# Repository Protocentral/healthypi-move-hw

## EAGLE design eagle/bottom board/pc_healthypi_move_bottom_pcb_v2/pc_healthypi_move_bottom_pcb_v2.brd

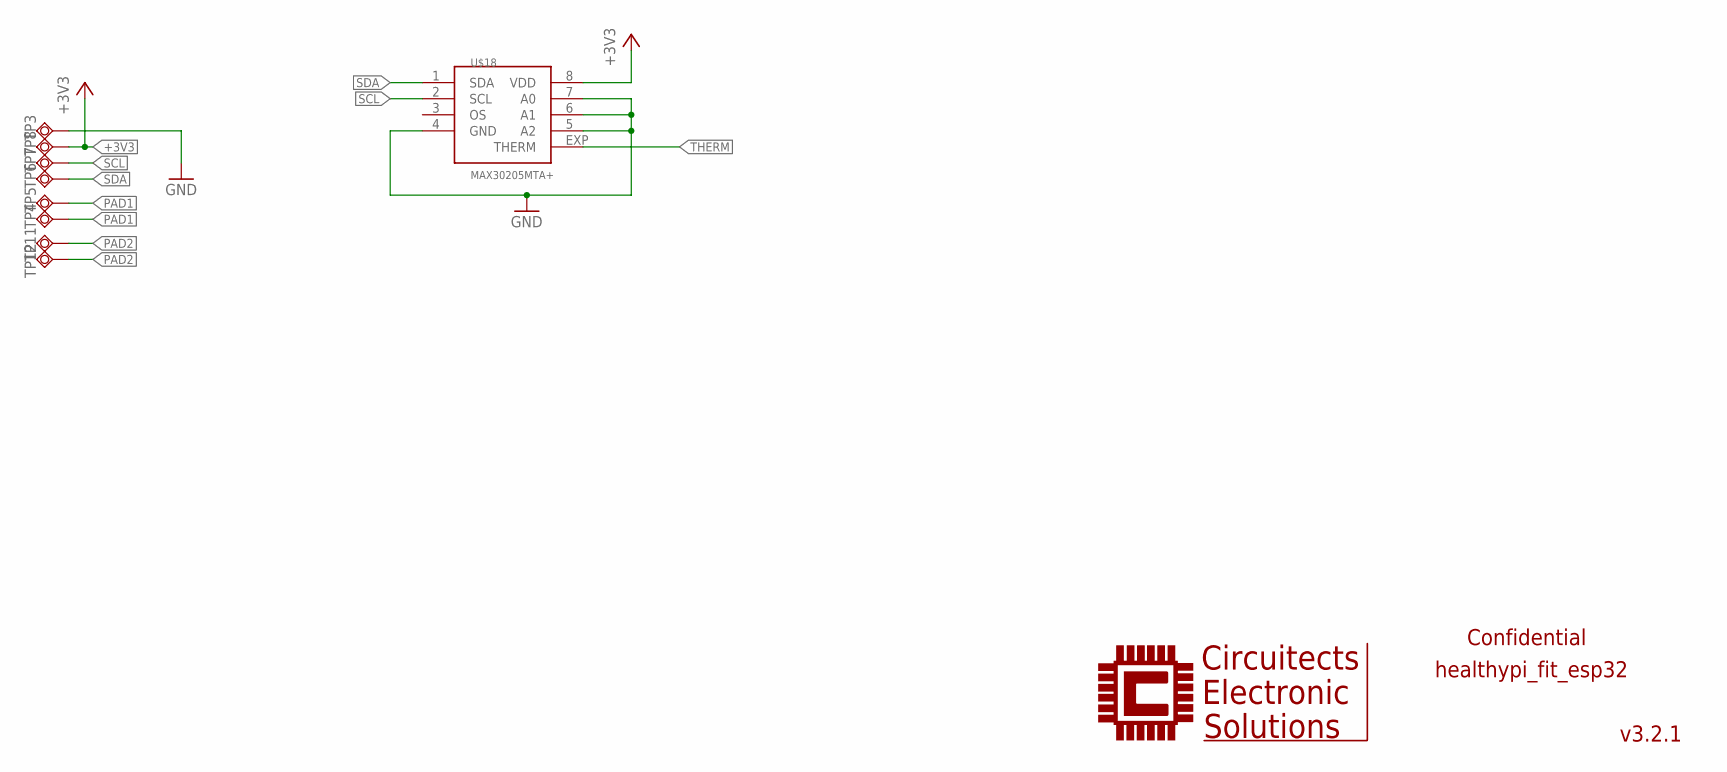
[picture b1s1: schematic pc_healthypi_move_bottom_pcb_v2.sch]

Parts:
TP3, TP4, TP5, TP6, TP7, TP8, TP11, TP12: TPSQTP20SQ; TP20SQ
U$18: MAX30205MTA+; TDFN-08

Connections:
+3V3: TP8.TP, U$18.8 (VDD)
GND: TP3.TP, U$18.4 (GND), U$18.5 (A2), U$18.6 (A1), U$18.7 (A0)
PAD1: TP4.TP, TP5.TP
PAD2: TP11.TP, TP12.TP
SCL: TP7.TP, U$18.2 (SCL)
SDA: TP6.TP, U$18.1 (SDA)
THERM: U$18.EXP (THERM)

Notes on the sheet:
v3.2.1
healthypi_fit_esp32
Confidential

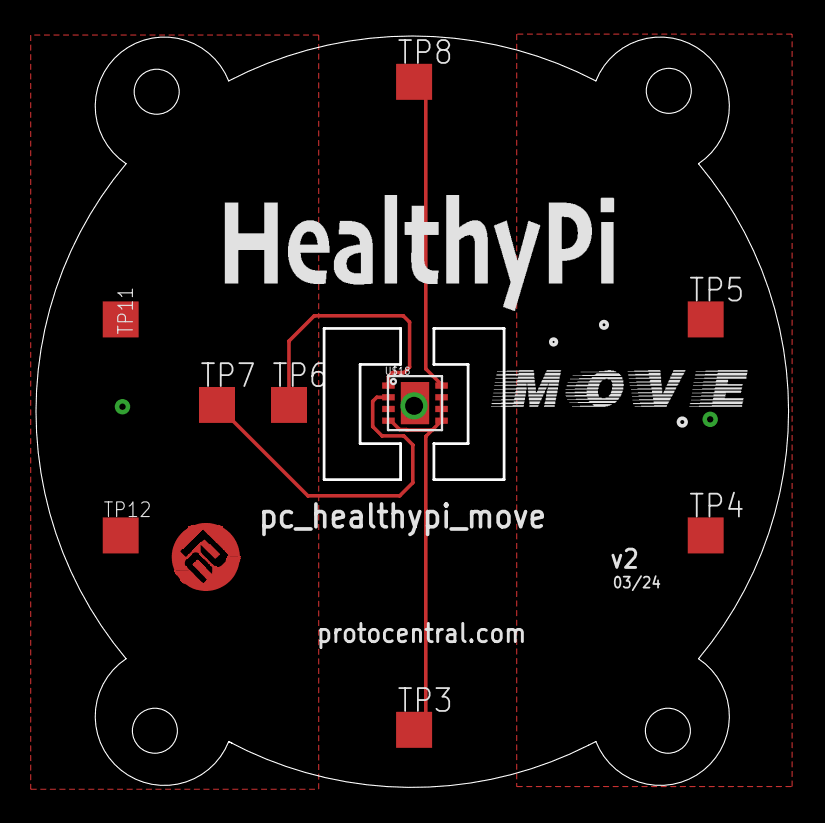
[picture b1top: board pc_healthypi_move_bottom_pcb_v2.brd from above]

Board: 2 copper layers, 41.8 x 41.7 mm, 14 parts (2 on the bottom side), 6 nets.

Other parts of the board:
U$2, U$5: HEALTHYPI_MOVE_LOGO
U$3, U$6: HEALTHYPI_MOVE_LOGO_1
U$51: PCROUNDLOGO_GOLD

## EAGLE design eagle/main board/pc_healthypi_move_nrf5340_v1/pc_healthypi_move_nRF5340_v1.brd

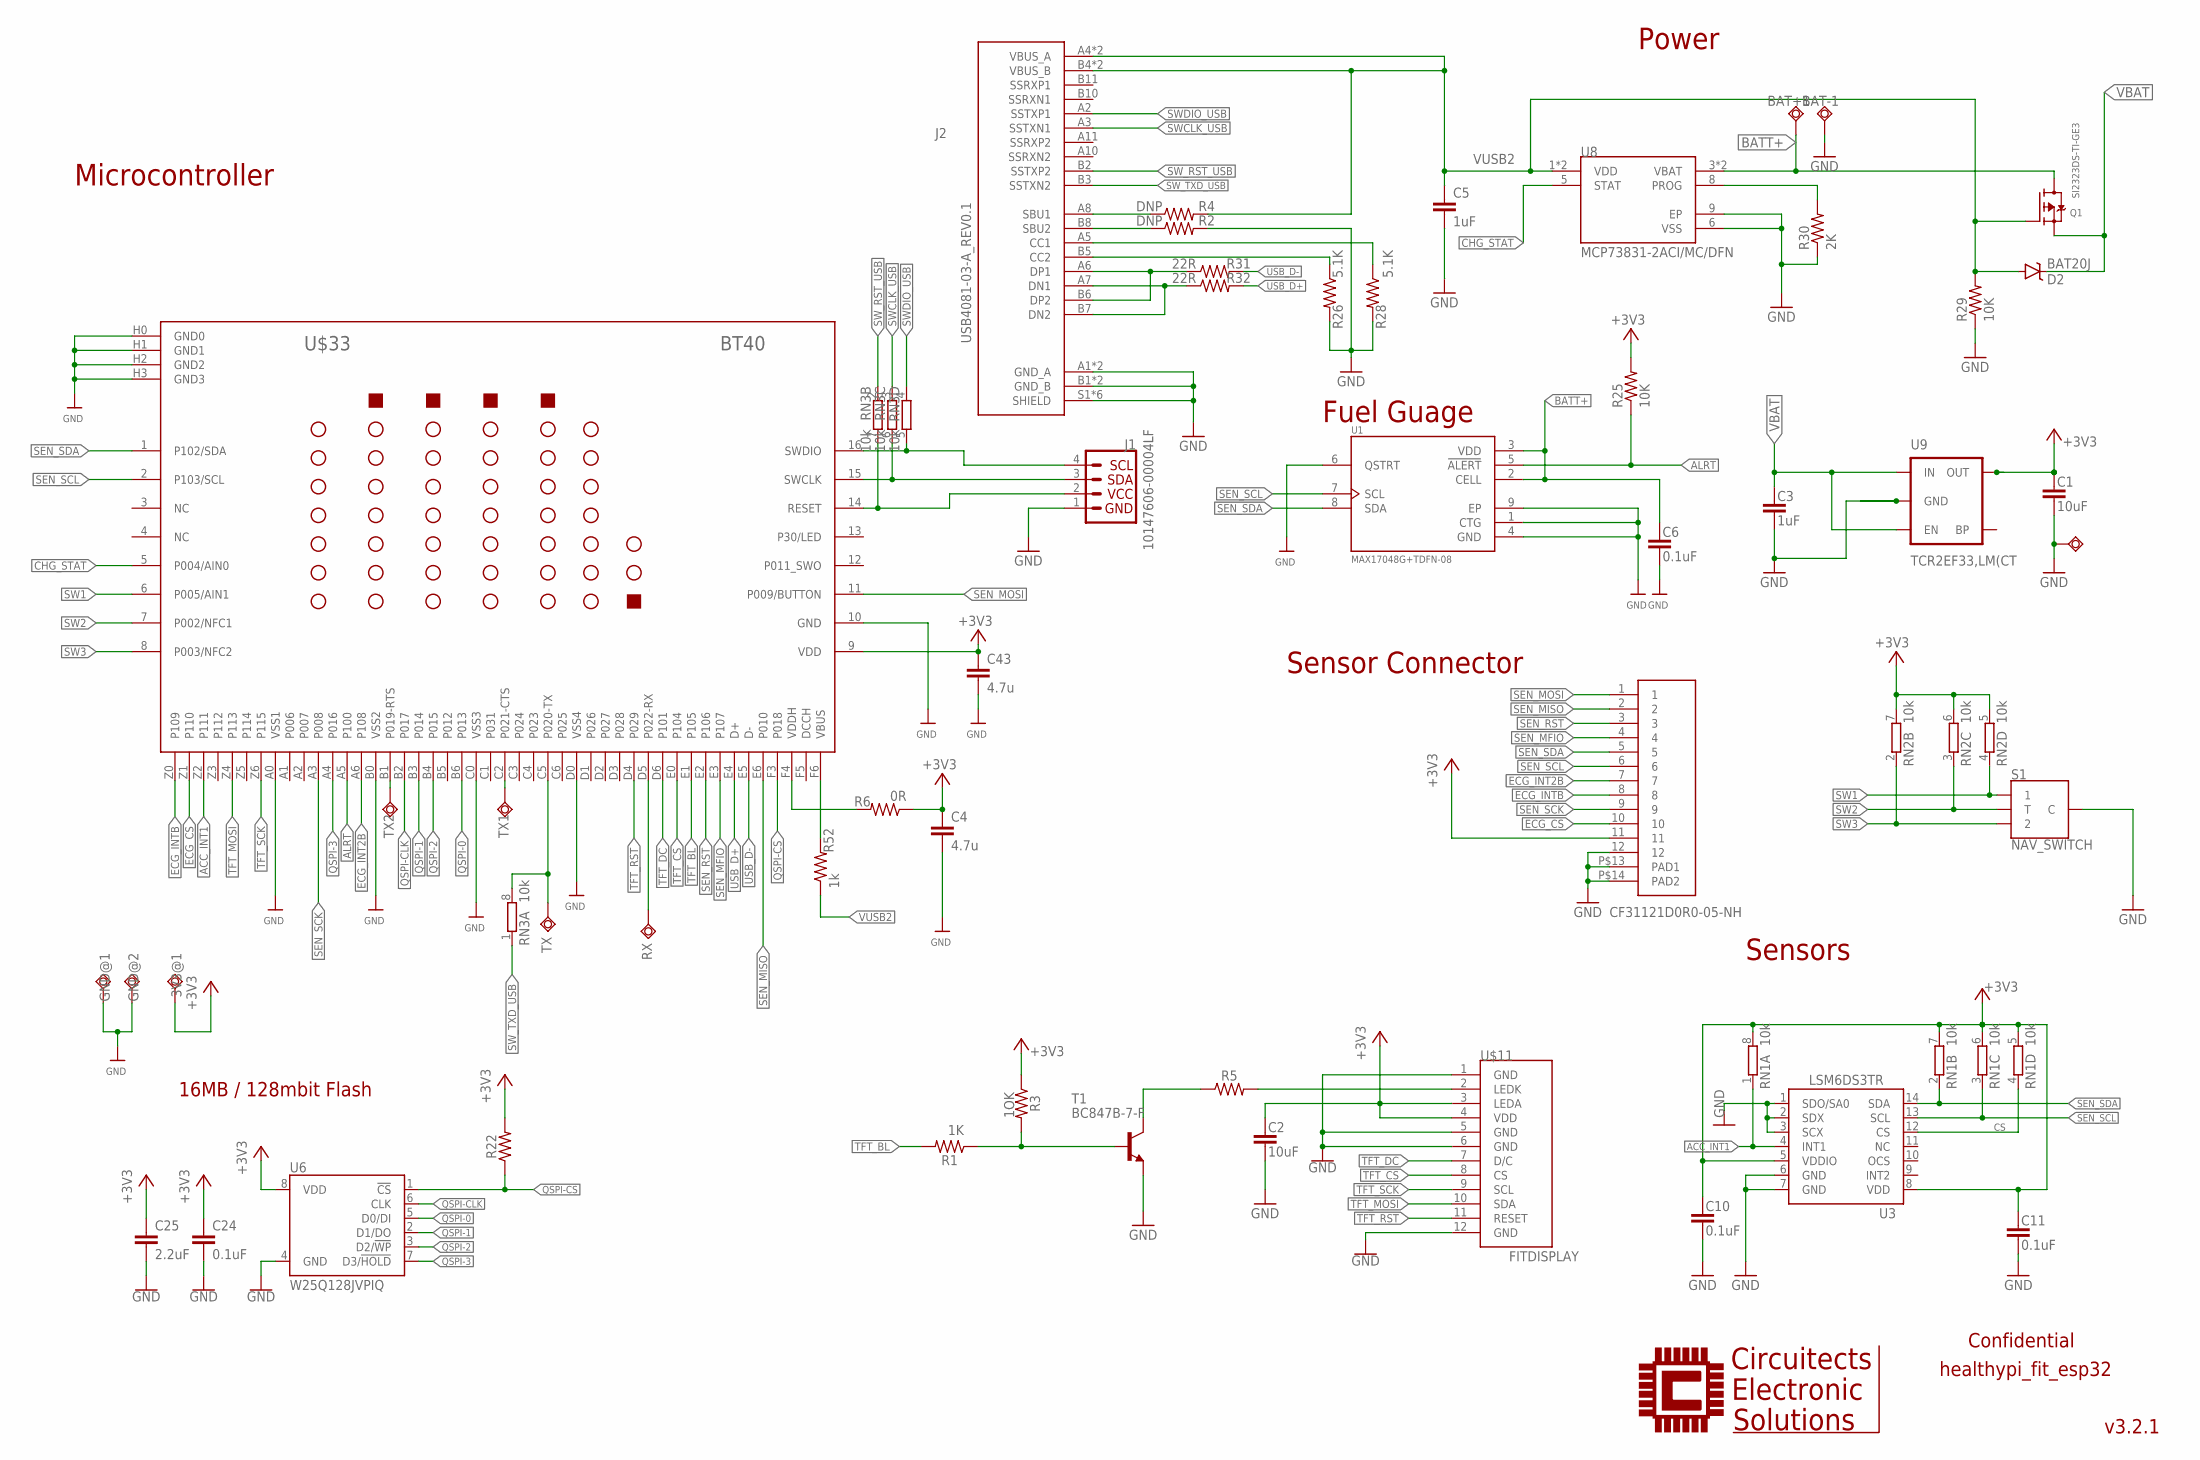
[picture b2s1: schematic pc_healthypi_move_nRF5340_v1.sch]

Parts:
3V3@1: TPSQTP13SQ; TP13SQ
BAT+1: TPSQTP13SQ; TP13SQ
BAT-1: TPSQTP13SQ; TP13SQ
C1, C2: 10uF; 0603@1
C3, C5: 1uF; 0402-TIGHT
C4, C43: 4.7u; C0402
C6, C10, C11, C24: 0.1uF; 0402-TIGHT
C25: 2.2uF; 0402-TIGHT
D2: BAT20J; SOD-323
GND@1, GND@2: TPSQTP13SQ; TP13SQ
J1: 10147606-00004LF; JST04_1MM_RA
J2: USB4081-03-A_REV0.1; GCT_USB4081-03-A_REV0.1
Q1: SI2323DS-TI-GE3; SOT23-R
R1, R3: 200; R0402
R2, R4: DNP; 0402-RES
R5: 200R; R0402
R6: 0R; 0402-RES
R22: 10k; R0402
R25: 10K; 0402-RES
R26, R28: 5.1K; 0402-RES
R29: 10K; R0402
R30: 2K; R0402
R31, R32: 22R; 0402-RES
R52: 1k; 0402-RES
RN1, RN2, RN3: 10k; 4X0402ARV341
RX: TPSQTP13SQ; TP13SQ
S1: NAV_SWITCH
SWIO6: TPSQTP11R; TP11R
T1: BC847B-7-F; SOT23-BEC
TX, TX1, TX2: TPSQTP13SQ; TP13SQ
U1: MAX17048G+TDFN-08; SON50P200X200X80-9N
U3: LSM6DS3TR; LGA14L
U6: W25Q128JVPIQ; WSON-8-6X5-SKINNY_CENTERPAD
U8: MCP73831-2ACI/MC/DFN; SON50P200X300X100-9N
U9: TCR2EF33,LM(CT; SOT23-5
U$5: CF31121D0R0-05-NH
U$11: FITDISPLAY
U$33: BT40

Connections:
+3V3: 3V3@1.TP, C1.1, C2.1, C4.1, C10.1, C11.1, C24.1, C25.1, C43.1, R3.1, R6.1, R22.2, R25.2, RN1.5 (2), RN1.6 (2), RN1.7 (2), RN1.8 (2), RN2.5 (2), RN2.6 (2), RN2.7 (2), U3.5 (VDDIO), U3.8 (VDD), U6.8 (VDD), U9.5 (OUT), U$5.11, U$11.3 (LEDA), U$11.4 (VDD), U$33.9 (VDD)
ACC_INT1: RN1.1, U3.4 (INT1), U$33.Z2 (P111)
ALRT: R25.1, U1.5 (!ALERT), U$33.A5 (P100)
BATT+: BAT+1.TP, C6.1, Q1.3 (D), U1.2 (CELL), U1.3 (VDD), U8.3 (VBAT), U8.4 (VBAT)
CHG_STAT: U8.5 (STAT), U$33.5 (P004/AIN0)
CS: RN1.4 (1), U3.12 (CS)
ECG_CS: U$5.10, U$33.Z1 (P110)
ECG_INT2B: U$5.7, U$33.A6 (P108)
ECG_INTB: U$5.8, U$33.Z0 (P109)
GND: BAT-1.TP, C1.2, C2.2, C3.2, C4.2, C5.2, C6.2, C10.2, C11.2, C24.2, C25.2, C43.2, GND@1.TP, GND@2.TP, J1.1, J2.A1 (GND_A), J2.A12 (GND_A), J2.B1 (GND_B), J2.B12 (GND_B), J2.S1 (SHIELD), J2.S2 (SHIELD), J2.S3 (SHIELD), J2.S4 (SHIELD), J2.S5 (SHIELD), J2.S6 (SHIELD), R2.2, R26.2, R28.2, R29.1, R30.1, S1.C, SWIO6.TP, T1.E, U1.1 (CTG), U1.4 (GND), U1.6 (QSTRT), U1.9 (EP), U3.1 (SDO/SA0), U3.2 (SDX), U3.3 (SCX), U3.6 (GND), U3.7 (GND), U6.4 (GND), U8.6 (VSS), U8.9 (EP), U9.2 (GND), U$5.12, U$5.P$13 (PAD1), U$5.P$14 (PAD2), U$11.1 (GND), U$11.5 (GND), U$11.6 (GND), U$11.12 (GND), U$33.10 (GND), U$33.A0 (VSS1), U$33.B0 (VSS2), U$33.C0 (VSS3), U$33.D0 (VSS4), U$33.H0 (GND0), U$33.H1 (GND1), U$33.H2 (GND2), U$33.H3 (GND3)
unnamed: J2.B8 (SBU2), R2.1
unnamed: J2.A8 (SBU1), R4.1
unnamed: TX2.TP, U$33.B1 (P019-RTS)
unnamed: J2.B5 (CC2), R26.1
unnamed: TX1.TP, U$33.C2 (P021-CTS)
unnamed: J2.A5 (CC1), R28.1
unnamed: R30.2, U8.8 (PROG)
unnamed: J2.A6 (DP1), J2.B6 (DP2), R31.1
unnamed: J2.A7 (DN1), J2.B7 (DN2), R32.1
unnamed: R5.2, U$11.2 (LEDK)
unnamed: R5.1, T1.C
unnamed: R1.1, R3.2, T1.B
unnamed: R52.2, U$33.F6 (VBUS)
unnamed: R6.2, U$33.F4 (VDDH)
QSPI-0: U6.5 (D0/DI), U$33.B6 (P013)
QSPI-1: U6.2 (D1/DO), U$33.B3 (P014)
QSPI-2: U6.3 (D2/!WP!), U$33.B4 (P015)
QSPI-3: U6.7 (D3/!HOLD!), U$33.A4 (P016)
QSPI-CLK: U6.6 (CLK), U$33.B2 (P017)
QSPI-CS: R22.1, U6.1 (!CS!), U$33.F3 (P018)
RESET1: J1.2, RN3.7 (2), U$33.14 (RESET)
SEN_MFIO: U$5.4, U$33.E3 (P107)
SEN_MISO: U$5.2, U$33.E6 (P010)
SEN_MOSI: U$5.1, U$33.11 (P009/BUTTON)
SEN_RST: U$5.3, U$33.E2 (P106)
SEN_SCK: U$5.9, U$33.A3 (P008)
SEN_SCL: RN1.3 (1), U1.7 (SCL), U3.13 (SCL), U$5.6, U$33.2 (P103/SCL)
SEN_SDA: RN1.2 (1), U1.8 (SDA), U3.14 (SDA), U$5.5, U$33.1 (P102/SDA)
SW1: RN2.4 (1), S1.1, U$33.6 (P005/AIN1)
SW2: RN2.3 (1), S1.T, U$33.7 (P002/NFC1)
SW3: RN2.2 (1), S1.2, U$33.8 (P003/NFC2)
SWCLK1: J1.3, RN3.6 (2), U$33.15 (SWCLK)
SWCLK_USB: J2.A3 (SSTXN1), RN3.3 (1)
SWDIO1: J1.4, RN3.5 (2), U$33.16 (SWDIO)
SWDIO_USB: J2.A2 (SSTXP1), RN3.4 (1)
SW_RST_USB: J2.B2 (SSTXP2), RN3.2 (1)
SW_TXD_USB: J2.B3 (SSTXN2), RN3.1
TFT_BL: R1.2, U$33.E1 (P105)
TFT_CS: U$11.8 (CS), U$33.E0 (P104)
TFT_DC: U$11.7 (D/C), U$33.D6 (P101)
TFT_MOSI: U$11.10 (SDA), U$33.Z4 (P113)
TFT_RST: U$11.11 (RESET), U$33.D4 (P029)
TFT_SCK: U$11.9 (SCL), U$33.Z6 (P115)
UART_RX: RX.TP, U$33.D5 (P022-RX)
UART_TX: RN3.8 (2), TX.TP, U$33.C5 (P020-TX)
USB_D+: R32.2, U$33.E4 (D+)
USB_D-: R31.2, U$33.E5 (D-)
VBAT: C3.1, D2.C, Q1.2 (S), U9.1 (IN), U9.3 (EN)
VUSB2: C5.1, D2.A, J2.A4 (VBUS_A), J2.A9 (VBUS_A), J2.B4 (VBUS_B), J2.B9 (VBUS_B), Q1.1 (G), R4.2, R29.2, R52.1, U8.1 (VDD), U8.2 (VDD)

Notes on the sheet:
v3.2.1
Power
healthypi_fit_esp32
Confidential
Fuel Guage
Sensors
Sensor Connector
16MB / 128mbit Flash
1OK
CF31121D0R0-05-NH
Microcontroller

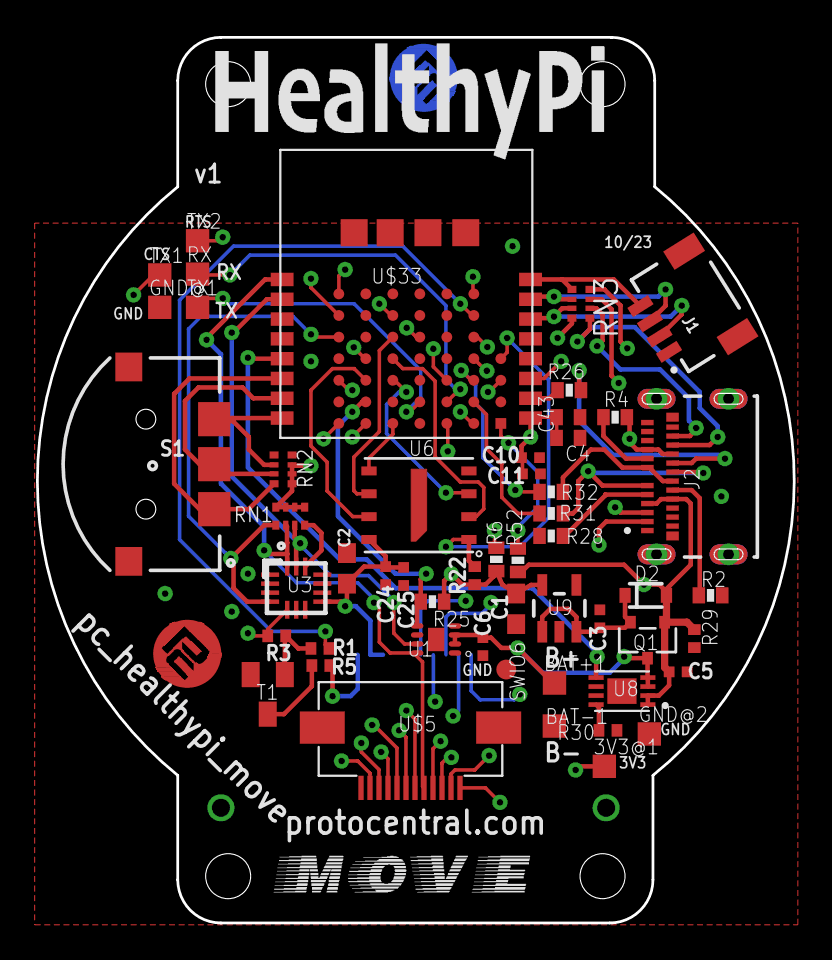
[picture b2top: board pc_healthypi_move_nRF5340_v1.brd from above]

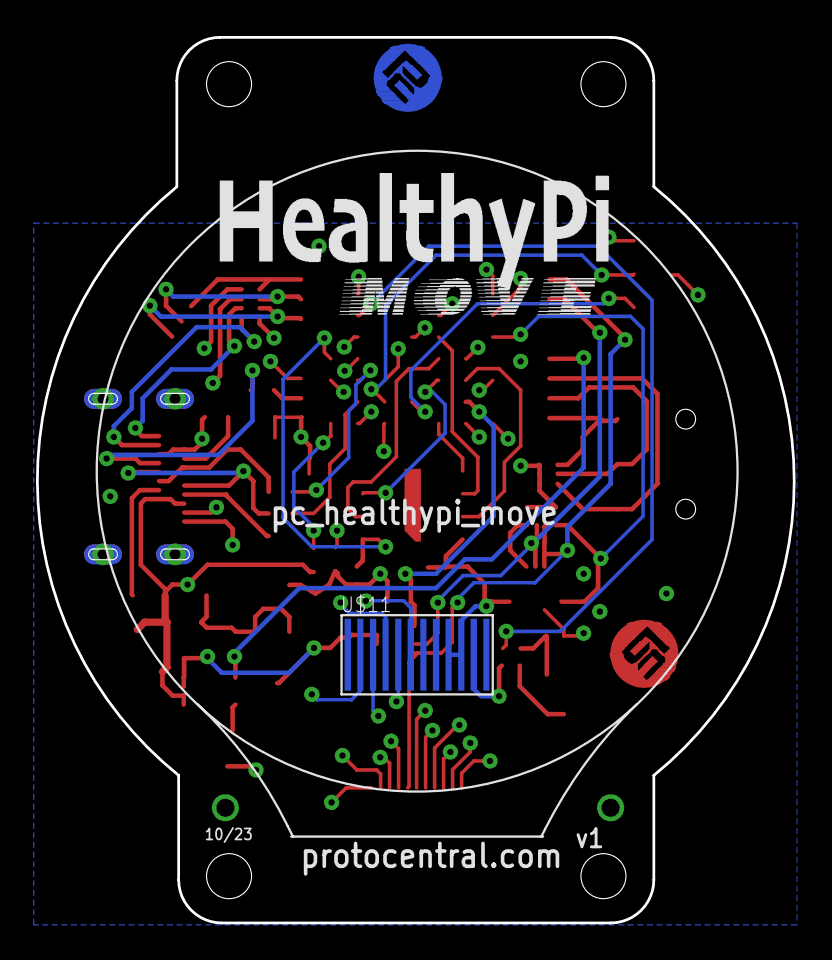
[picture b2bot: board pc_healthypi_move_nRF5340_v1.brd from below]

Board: 4 copper layers, 42.0 x 49.2 mm, 59 parts (4 on the bottom side), 59 nets.

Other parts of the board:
U$1, U$13: HEALTHYPI_MOVE_LOGO
U$6, U$10: HEALTHYPI_MOVE_LOGO_1
U$14, U$15: PCROUNDLOGO_GOLD

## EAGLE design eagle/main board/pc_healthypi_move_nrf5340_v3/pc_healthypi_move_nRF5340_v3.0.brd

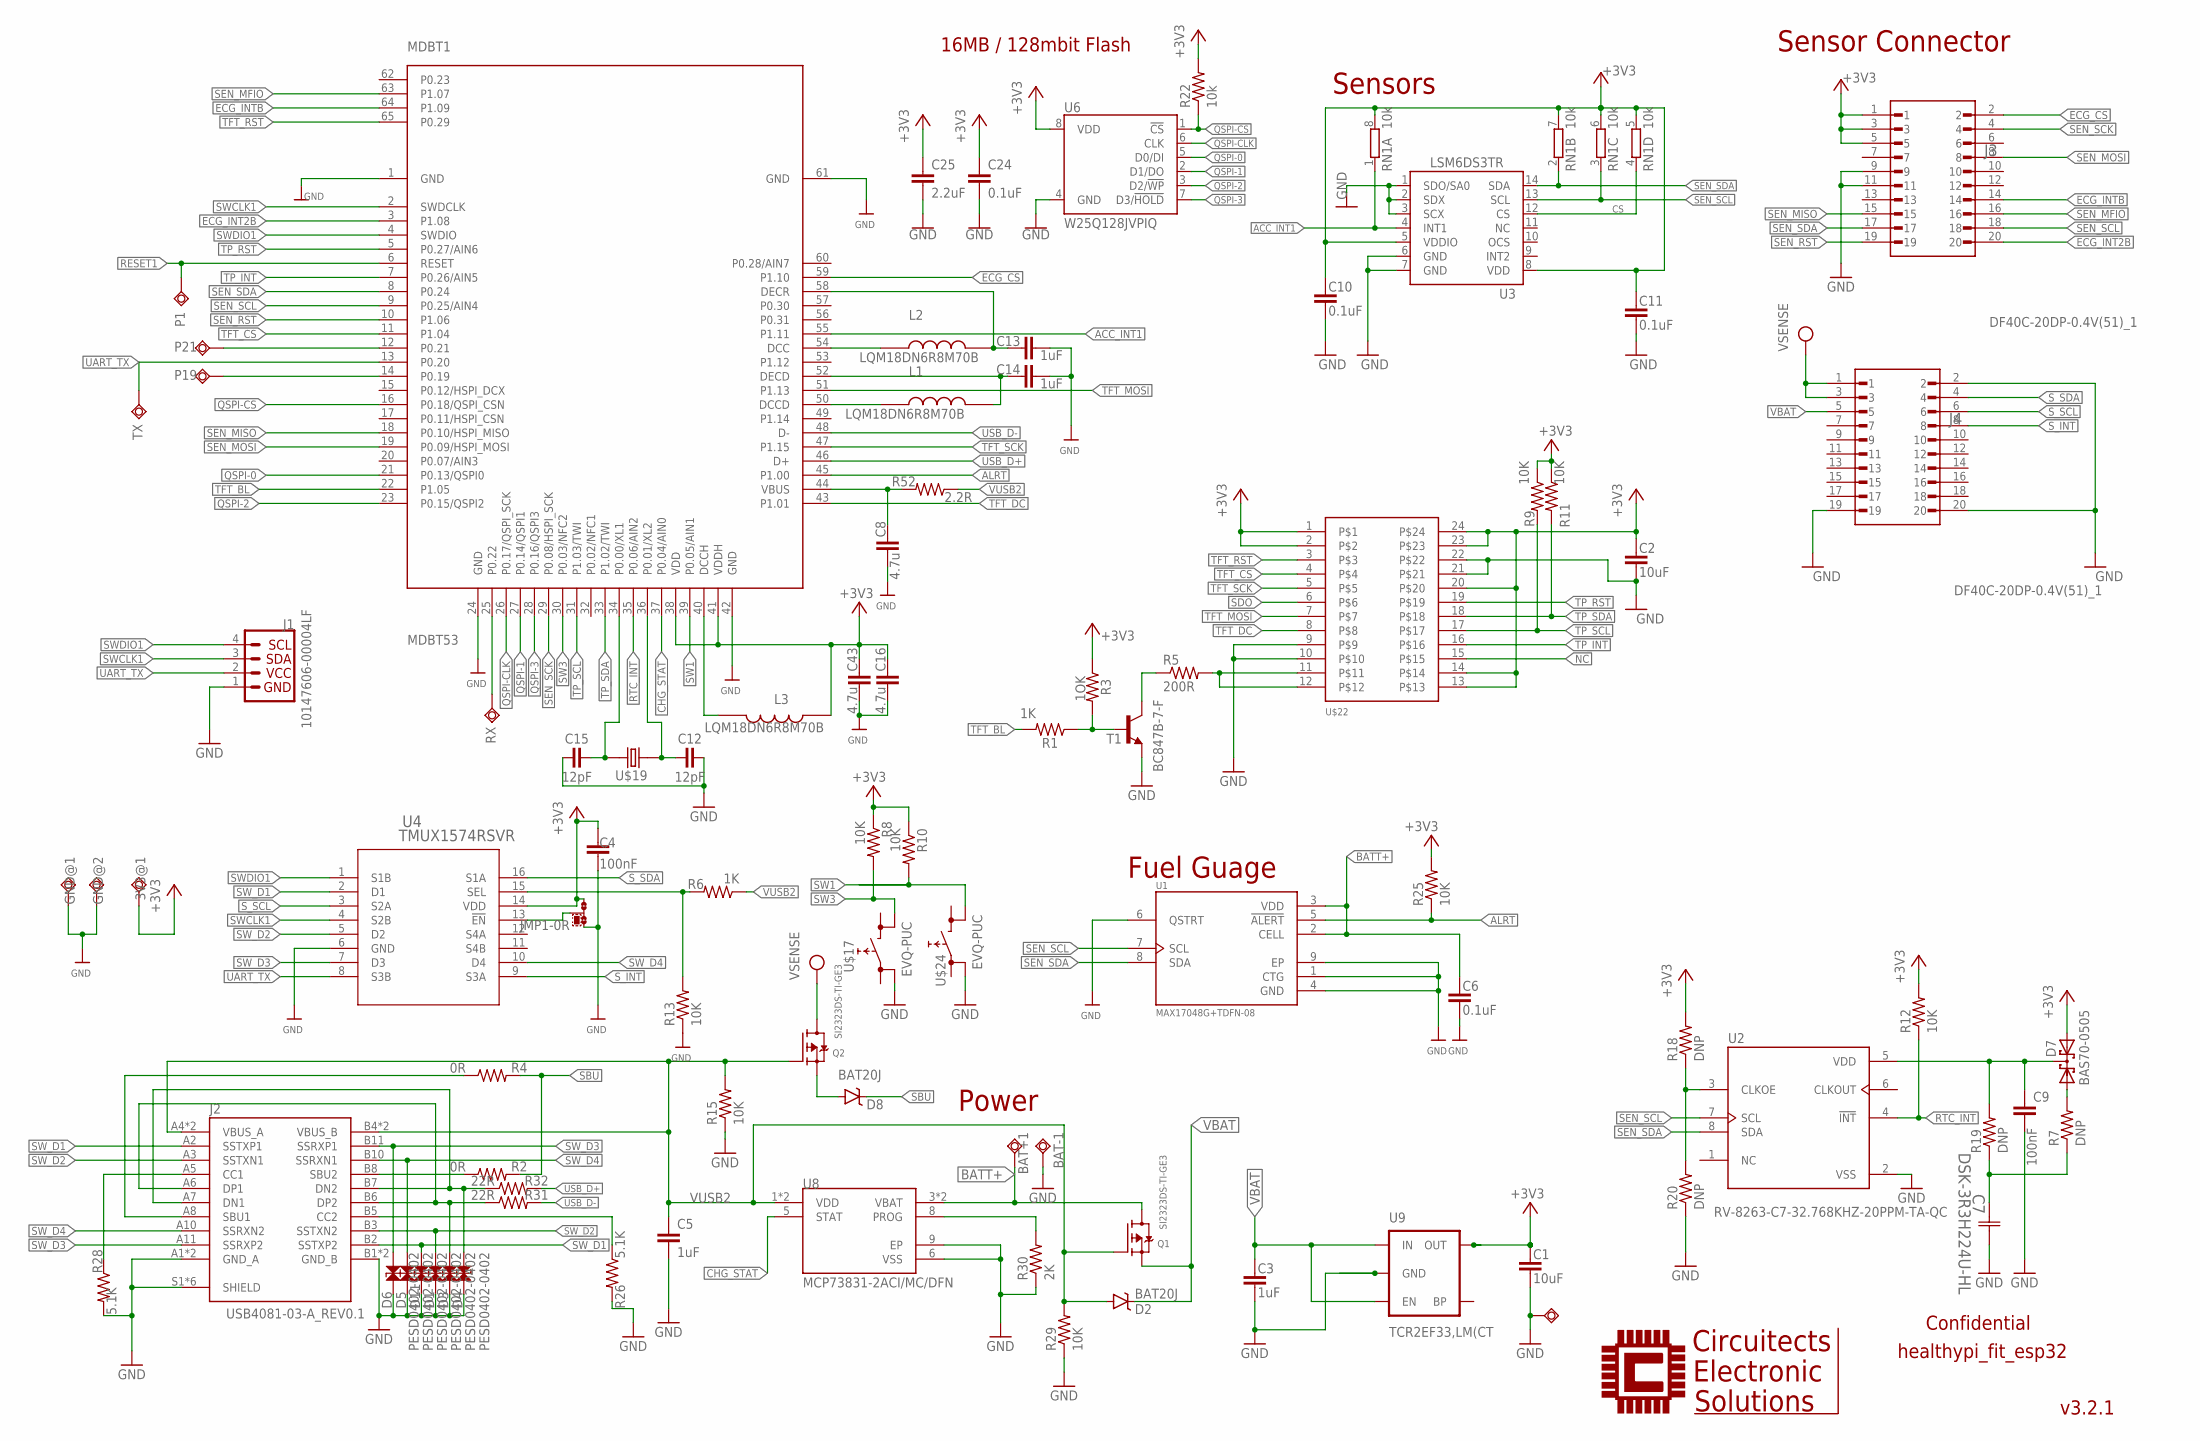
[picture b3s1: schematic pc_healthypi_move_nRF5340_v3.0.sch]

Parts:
3V3@1: TPSQTP13SQ; TP13SQ
BAT+1: TPSQTP13SQ; TP13SQ
BAT-1: TPSQTP13SQ; TP13SQ
C1, C2: 10uF; 0603@1
C3, C5, C13, C14: 1uF; 0402-TIGHT
C4: 100nF; 0402-TIGHT
C6, C10, C11, C24: 0.1uF; 0402-TIGHT
C7: DSK-3R3H224U-HL; CAP_DSK-3R3H224U-HL_ELN
C8, C16, C43: 4.7u; C0402
C9: 100nF; C0402
C12, C15: 12pF; C0402
C25: 2.2uF; 0402-TIGHT
D1, D3, D4, D5, D6, D11: PESD0402-0402; 0402
D2, D8: BAT20J; SOD-323
D7: BAS70-0505; SOT23
GND@1, GND@2: TPSQTP13SQ; TP13SQ
J1: 10147606-00004LF; JST04_1MM_RA
J2: USB4081-03-A_REV0.1; GCT_USB4081-03-A_REV0.1
J3, J4: DF40C-20DP-0.4V(51)_1; HRS_DF40C-20DP-0.4V(51)
JMP1: 0R-JUMPB; B0R-JMP
L1, L2, L3: LQM18DN6R8M70B; INDC1608X95N
MDBT1: MDBT53
P1, P19, P21: TPSQTP13SQ; TP13SQ
Q1, Q2: SI2323DS-TI-GE3; SOT23-R
R1, R3: 200; R0402
R2, R4: 0R; 0402-RES
R5: 200R; R0402
R6: 1K; 0402-RES
R7, R18, R19, R20: DNP; R0402
R8, R9, R10, R11, R12, R13, R15, R29: 10K; R0402
R22: 10k; R0402
R25: 10K; 0402-RES
R26, R28: 5.1K; 0402-RES
R30: 2K; R0402
R31, R32: 22R; 0402-RES
R52: 2.2R; 0402-RES
RN1: 10k; 4X0402ARV341
RX: TPSQTP13SQ; TP13SQ
SWIO6: TPSQTP11R; TP11R
T1: BC847B-7-F; SOT23-BEC
TX: TPSQTP13SQ; TP13SQ
U1: MAX17048G+TDFN-08; SON50P200X200X80-9N
U2: RV-8263-C7-32.768KHZ-20PPM-TA-QC; IC_RV-8263-C7-32.768KHZ-20PPM-TA-QC
U3: LSM6DS3TR; LGA14L
U4: TMUX1574RSVR; RSV16_TEX
U6: W25Q128JVPIQ; WSON-8-6X5-SKINNY_CENTERPAD
U8: MCP73831-2ACI/MC/DFN; SON50P200X300X100-9N
U9: TCR2EF33,LM(CT; SOT23-5
U$17, U$24: EVQ-PUC
U$19: 520-327-12.5-34B(32.768KHZ); ECX-31B
U$22: AXT524124

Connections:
+3V3: 3V3@1.TP, C1.1, C2.1, C4.1, C10.1, C11.1, C16.1, C24.1, C25.1, C43.1, D7.2 (A2), J3.1, J3.3, J3.5, JMP1.3, L3.1, MDBT1.38 (VDD), MDBT1.41 (VDDH), R3.1, R8.1, R9.1, R10.1, R11.1, R12.2, R18.2, R22.2, R25.2, RN1.5 (2), RN1.6 (2), RN1.7 (2), RN1.8 (2), U3.5 (VDDIO), U3.8 (VDD), U4.14 (VDD), U6.8 (VDD), U9.5 (OUT), U$22.1, U$22.2, U$22.13, U$22.14, U$22.20, U$22.23, U$22.24
ACC_INT1: MDBT1.55 (P1.11), RN1.1, U3.4 (INT1)
ALRT: MDBT1.45 (P1.00), R25.1, U1.5 (!ALERT)
BATT+: BAT+1.TP, C6.1, Q1.3 (D), U1.2 (CELL), U1.3 (VDD), U8.3 (VBAT), U8.4 (VBAT)
CHG_STAT: MDBT1.37 (P0.04/AIN0), U8.5 (STAT)
CS: RN1.4 (1), U3.12 (CS)
ECG_CS: J3.2, MDBT1.59 (P1.10)
ECG_INT2B: J3.20, MDBT1.3 (P1.08)
ECG_INTB: J3.14, MDBT1.64 (P1.09)
GND: BAT-1.TP, C1.2, C2.2, C3.2, C4.2, C5.2, C6.2, C7.1, C8.2, C9.2, C10.2, C11.2, C12.2, C13.2, C14.2, C15.1, C16.2, C24.2, C25.2, C43.2, D1.1, D3.1, D4.1, D5.1, D6.1, D11.1, GND@1.TP, GND@2.TP, J1.1, J2.A1 (GND_A), J2.A12 (GND_A), J2.B1 (GND_B), J2.B12 (GND_B), J2.S1 (SHIELD), J2.S2 (SHIELD), J2.S3 (SHIELD), J2.S4 (SHIELD), J2.S5 (SHIELD), J2.S6 (SHIELD), J3.9, J3.11, J4.2, J4.19, J4.20, JMP1.1, MDBT1.1 (GND), MDBT1.24 (GND), MDBT1.42 (GND), MDBT1.61 (GND), R13.1, R15.1, R20.1, R26.2, R28.2, R29.1, R30.1, SWIO6.TP, T1.E, U1.1 (CTG), U1.4 (GND), U1.6 (QSTRT), U1.9 (EP), U2.2 (VSS), U3.1 (SDO/SA0), U3.2 (SDX), U3.3 (SCX), U3.6 (GND), U3.7 (GND), U4.6 (GND), U6.4 (GND), U8.6 (VSS), U8.9 (EP), U9.2 (GND), U$17.3 (0), U$22.9, U$22.10, U$22.21, U$22.22, U$24.3 (0)
unnamed: J2.B8 (SBU2), R2.1
unnamed: J2.A8 (SBU1), R4.1
unnamed: J2.B5 (CC2), R26.1
unnamed: MDBT1.12 (P0.21), P21.TP
unnamed: J2.A5 (CC1), R28.1
unnamed: R30.2, U8.8 (PROG)
unnamed: D3.2, J2.A6 (DP1), J2.B6 (DP2), R31.1
unnamed: D4.2, J2.A7 (DN1), J2.B7 (DN2), R32.1
unnamed: R5.2, U$22.11, U$22.12
unnamed: R5.1, T1.C
unnamed: R1.1, R3.2, T1.B
unnamed: C8.1, MDBT1.44 (VBUS), R52.2
unnamed: R6.2, R13.2, U4.15 (SEL)
unnamed: C15.2, MDBT1.34 (P0.00/XL1), U$19.P$2 (2)
unnamed: C9.1, D7.3 (K1K2), R19.2, U2.5 (VDD)
unnamed: R18.1, R20.2, U2.3 (CLKOE)
unnamed: D7.1 (A1), R7.2
unnamed: C7.2, R7.1, R19.1
unnamed: C12.1, MDBT1.36 (P0.01/XL2), U$19.P$1 (1)
unnamed: MDBT1.25 (P0.22), RX.TP
unnamed: L3.2, MDBT1.40 (DCCH)
unnamed: JMP1.2, U4.13 (!EN)
unnamed: L1.1, MDBT1.50 (DCCD)
unnamed: C14.1, L1.2, MDBT1.52 (DECD)
unnamed: L2.1, MDBT1.54 (DCC)
unnamed: C13.1, L2.2, MDBT1.58 (DECR)
unnamed: D8.A, Q2.2 (S)
NC: U$22.15
P19: MDBT1.14 (P0.19), P19.TP
QSPI-0: MDBT1.21 (P0.13/QSPI0), U6.5 (D0/DI)
QSPI-1: MDBT1.27 (P0.14/QSPI1), U6.2 (D1/DO)
QSPI-2: MDBT1.23 (P0.15/QSPI2), U6.3 (D2/!WP!)
QSPI-3: MDBT1.28 (P0.16/QSPI3), U6.7 (D3/!HOLD!)
QSPI-CLK: MDBT1.26 (P0.17/QSPI_SCK), U6.6 (CLK)
QSPI-CS: MDBT1.16 (P0.18/QSPI_CSN), R22.1, U6.1 (!CS!)
RESET1: MDBT1.6 (RESET), P1.TP
RTC_INT: MDBT1.35 (P0.06/AIN2), R12.1, U2.4 (!INT)
SBU: D8.C, R2.2, R4.2
SDO: U$22.6
SEN_MFIO: J3.16, MDBT1.63 (P1.07)
SEN_MISO: J3.15, MDBT1.18 (P0.10/HSPI_MISO)
SEN_MOSI: J3.8, MDBT1.19 (P0.09/HSPI_MOSI)
SEN_RST: J3.19, MDBT1.10 (P1.06)
SEN_SCK: J3.4, MDBT1.29 (P0.08/HSPI_SCK)
SEN_SCL: J3.18, MDBT1.9 (P0.25/AIN4), RN1.3 (1), U1.7 (SCL), U2.7 (SCL), U3.13 (SCL)
SEN_SDA: J3.17, MDBT1.8 (P0.24), RN1.2 (1), U1.8 (SDA), U2.8 (SDA), U3.14 (SDA)
SW1: MDBT1.39 (P0.05/AIN1), R10.2, U$24.2 (1)
SW3: MDBT1.30 (P0.03/NFC2), R8.2, U$17.2 (1)
SWCLK1: J1.3, MDBT1.2 (SWDCLK), U4.4 (S2B)
SWDIO1: J1.4, MDBT1.4 (SWDIO), U4.1 (S1B)
SW_D1: D11.2, J2.A2 (SSTXP1), J2.B2 (SSTXP2), U4.2 (D1)
SW_D2: D1.2, J2.A3 (SSTXN1), J2.B3 (SSTXN2), U4.5 (D2)
SW_D3: D6.2, J2.A11 (SSRXP2), J2.B11 (SSRXP1), U4.7 (D3)
SW_D4: D5.2, J2.A10 (SSRXN2), J2.B10 (SSRXN1), U4.10 (D4)
S_INT: J4.8, U4.9 (S3A)
S_SCL: J4.6, U4.3 (S2A)
S_SDA: J4.4, U4.16 (S1A)
TFT_BL: MDBT1.22 (P1.05), R1.2
TFT_CS: MDBT1.11 (P1.04), U$22.4
TFT_DC: MDBT1.43 (P1.01), U$22.8
TFT_MOSI: MDBT1.51 (P1.13), U$22.7
TFT_RST: MDBT1.65 (P0.29), U$22.3
TFT_SCK: MDBT1.47 (P1.15), U$22.5
TP_INT: MDBT1.7 (P0.26/AIN5), U$22.16
TP_RST: MDBT1.5 (P0.27/AIN6), U$22.19
TP_SCL: MDBT1.31 (P1.03/TWI), R9.2, U$22.17
TP_SDA: MDBT1.33 (P1.02/TWI), R11.2, U$22.18
UART_TX: J1.2, MDBT1.13 (P0.20), TX.TP, U4.8 (S3B)
USB_D+: MDBT1.46 (D+), R32.2
USB_D-: MDBT1.48 (D-), R31.2
VBAT: C3.1, D2.C, J4.5, Q1.2 (S), U9.1 (IN), U9.3 (EN)
VPP: J4.1, J4.3, Q2.3 (D)
VUSB2: C5.1, D2.A, J2.A4 (VBUS_A), J2.A9 (VBUS_A), J2.B4 (VBUS_B), J2.B9 (VBUS_B), Q1.1 (G), Q2.1 (G), R6.1, R15.2, R29.2, R52.1, U8.1 (VDD), U8.2 (VDD)

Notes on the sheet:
v3.2.1
Power
healthypi_fit_esp32
Confidential
Fuel Guage
Sensors
Sensor Connector
16MB / 128mbit Flash
1OK

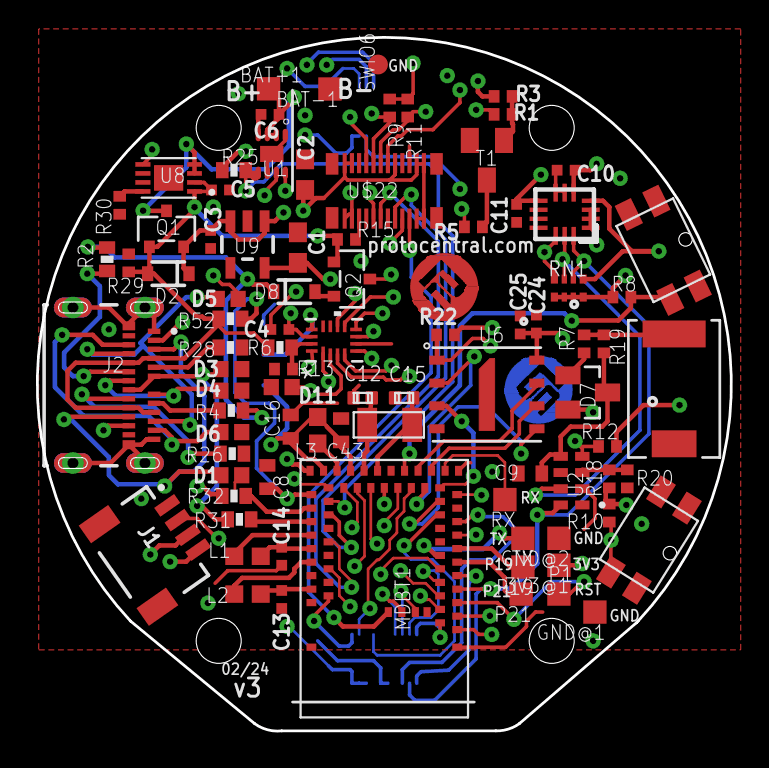
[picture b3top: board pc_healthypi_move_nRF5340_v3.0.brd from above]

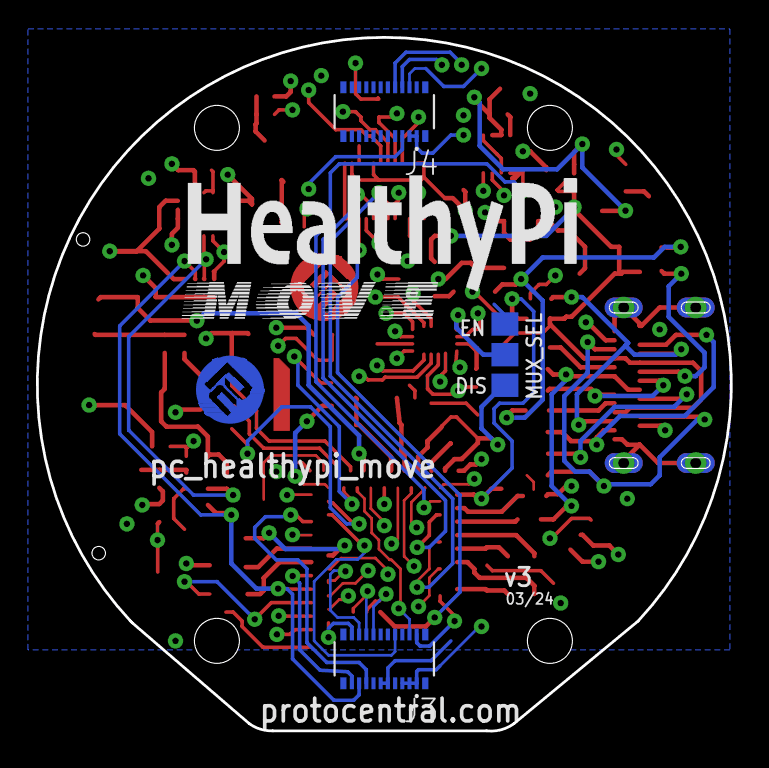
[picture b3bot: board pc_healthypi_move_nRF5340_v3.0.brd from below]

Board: 4 copper layers, 38.5 x 38.5 mm, 93 parts (6 on the bottom side), 81 nets.

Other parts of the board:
U$1, U$10: PCROUNDLOGO_GOLD
U$6: HEALTHYPI_MOVE_LOGO_1
U$13: HEALTHYPI_MOVE_LOGO

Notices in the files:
parts and their libraries:
microbuilder: This work is placed in the public domain, and may be freely used for commercial and non-commercial work with the following conditions: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
SparkFun-DiscreteSemi: Licensing: Creative Commons ShareAlike 4.0 International - https://creativecommons.org/licenses/by-sa/4.0
